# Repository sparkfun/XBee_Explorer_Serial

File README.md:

SparkFun XBee Explorer Serial
==============================

[*SparkFun XBee Explorer Serial (WRL-13225)*](https://www.sparkfun.com/products/9111)

This is a RS232 to serial base unit for the XBee line. 
It works with all XBee units, including Series 1, Series 2.5, standard and Pro versions.

Repository Contents
-------------------

* **/Hardware** - All Eagle design files (.brd, .sch, .STL)
* **/Production** - Production panel files (.brd)

Documentation
--------------
* **[Hookup Guide](https://learn.sparkfun.com/tutorials/exploring-xbees-and-xctu)** - Basic hookup guide for the XBee Serial Explorer.
* **[SparkFun Fritzing repo](https://github.com/sparkfun/Fritzing_Parts)** - Fritzing diagrams for SparkFun products.
* **[SparkFun 3D Model repo](https://github.com/sparkfun/3D_Models)** - 3D models of SparkFun products. 

Product Versions
----------------
* [WRL-13225](https://www.sparkfun.com/products/13225)- Version 1.4. Currently for sale. 
* [RWRL-09111](https://www.sparkfun.com/products/retired/9111)- Version 1.2. Retired. 

GitHub Version History
---------------
* [v1.4](https://github.com/sparkfun/XBee_Explorer_Serial/tree/v1.4) - Version 1.4. Current files. 
* [v1.3](https://github.com/sparkfun/XBee_Explorer_Serial/tree/v1.3) - Version 1.3. Retired.  
* [v1.2](https://github.com/sparkfun/XBee_Explorer_Serial/tree/v1.2) - Version 1.2. Retired. 

License Information
-------------------

This product is _**open source**_! 

Please review the LICENSE.md file for license information. 

If you have any questions or concerns on licensing, please contact techsupport@sparkfun.com.

Distributed as-is; no warranty is given.

- Your friends at SparkFun.

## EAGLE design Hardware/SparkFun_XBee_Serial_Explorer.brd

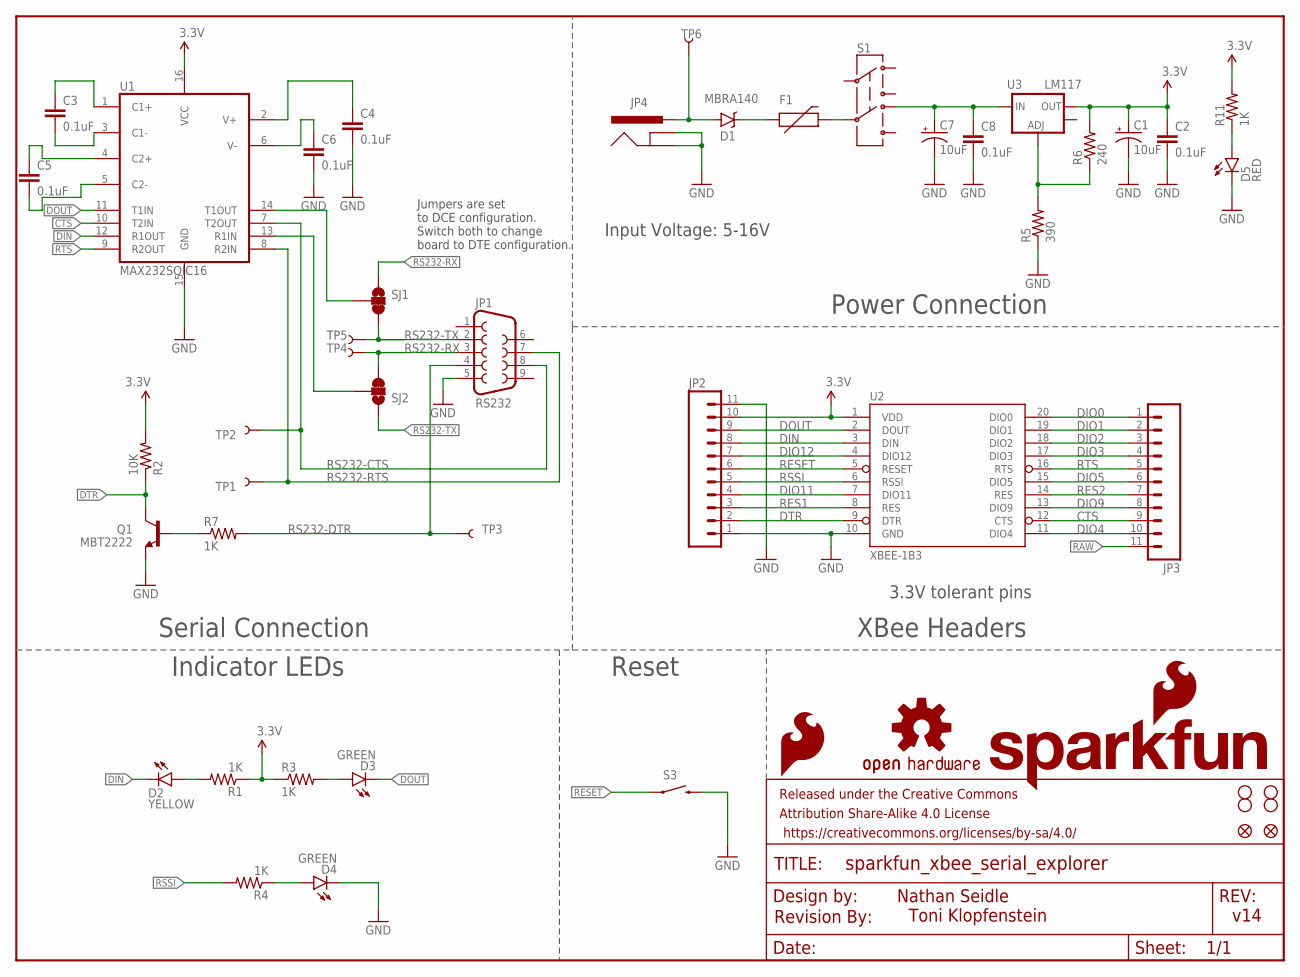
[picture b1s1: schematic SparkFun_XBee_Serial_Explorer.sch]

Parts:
C1, C7: 10uF; EIA3216
C2, C3, C4, C5, C6, C8: 0.1uF; 0603-CAP
D1: MBRA140; SMA-DIODE
D2: YELLOW; LED-1206
D3, D4: GREEN; LED-1206
D5: RED; LED-1206
F1: PTCTHERMISTOR1206; PTC-1206
FRAME1: FRAME-LETTER; CREATIVE_COMMONS
JP1: RS232; DB9
JP2, JP3: M11PTH; 1X11
JP4: POWER_JACKPTH_LOCK; POWER_JACK_PTH_LOCK
LOGO1: OSHW-LOGOL; OSHW-LOGO-L
LOGO2: SFE_LOGO_NAME_FLAME.2_INCH; SFE_LOGO_NAME_FLAME_.2
LOGO3: SFE_LOGO_FLAME.1_INCH; SFE_LOGO_FLAME_.1
Q1: MBT2222; SOT23-3
R1, R3, R4, R7, R11: 1K; 0603-RES
R2: 10K; 0603-RES
R5: 390; 0603-RES
R6: 240; 0603-RES
S1: AYZ0202
S3: TAC_SWITCHSMD; TACTILE-SWITCH-SMD
SJ1, SJ2: JUMPER-PAD-3-2OF3_NC_BY_TRACE_SMALL; PAD-JUMPER-3-2OF3_NC_BY_TRACE_YES_SILK_FULL_BOX
TP1, TP2, TP3, TP4, TP5, TP6: TEST-POINTTP_15TH_THRU; TP_15TH
U1: MAX232SOIC16; SO016
U2: XBEE-1B3; XBEE-SMD
U3: LM117; SOT223
U$1: REVISION
U$5, U$9, U$10, U$11: STAND-OFF
U$7, U$16: FIDUCIAL1X2; FIDUCIAL-1X2

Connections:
3.3V: C1.A (+), C2.1, JP2.10, R1.1, R2.2, R3.1, R6.2, R11.2, U1.16 (VCC), U2.1 (VDD), U3.2 (OUT)
CTS: JP3.9, U1.10 (T2IN), U2.12 (CTS)
DIN: D2.C, JP2.8, U1.12 (R1OUT), U2.3 (DIN)
DIO0: JP3.1, U2.20 (DIO0)
DIO1: JP3.2, U2.19 (DIO1)
DIO2: JP3.3, U2.18 (DIO2)
DIO3: JP3.4, U2.17 (DIO3)
DIO4: JP3.10, U2.11 (DIO4)
DIO5: JP3.6, U2.15 (DIO5)
DIO9: JP3.8, U2.13 (DIO9)
DIO11: JP2.4, U2.7 (DIO11)
DIO12: JP2.7, U2.4 (DIO12)
DOUT: D3.C, JP2.9, U1.11 (T1IN), U2.2 (DOUT)
DTR: JP2.2, Q1.3 (C), R2.1, U2.9 (DTR)
GND: C1.C (-), C2.2, C4.2, C6.2, C7.C (-), C8.2, D4.C, D5.C, JP1.5, JP2.1, JP2.11, JP4.GND, JP4.GNDBREAK, Q1.2 (E), R5.1, S3.3 (2), S3.4 (2), U1.15 (GND), U2.10 (GND)
unnamed: D2.A, R1.2
unnamed: D4.A, R4.1
unnamed: C3.1, U1.1 (C1+)
unnamed: D3.A, R3.2
unnamed: C3.2, U1.3 (C1-)
unnamed: C5.1, U1.4 (C2+)
unnamed: C5.2, U1.5 (C2-)
unnamed: C6.1, U1.6 (V-)
unnamed: C4.1, U1.2 (V+)
unnamed: R5.2, R6.1, U3.1 (ADJ)
unnamed: F1.2, S1.5
unnamed: Q1.1 (B), R7.1
unnamed: SJ2.2, U1.13 (R1IN)
unnamed: SJ1.2, U1.14 (T1OUT)
unnamed: D1.A, JP4.PWR, TP6.P$1
unnamed: D1.C, F1.1
unnamed: D5.A, R11.1
RAW: C7.A (+), C8.1, JP3.11, S1.6 (4), U3.3 (IN)
RES1: JP2.3, U2.8 (RES)
RES2: JP3.7, U2.14 (RES)
RESET: JP2.6, S3.1, S3.2 (1), U2.5 (RESET)
RS232-CTS: JP1.8, TP2.P$1, U1.7 (T2OUT)
RS232-DTR: JP1.4, R7.2, TP3.P$1
RS232-RTS: JP1.7, TP1.P$1, U1.8 (R2IN)
RS232-RX: JP1.3, SJ1.1, SJ2.3, TP4.P$1
RS232-TX: JP1.2, SJ1.3, SJ2.1, TP5.P$1
RSSI: JP2.5, R4.2, U2.6 (RSSI)
RTS: JP3.5, U1.9 (R2OUT), U2.16 (RTS)

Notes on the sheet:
v14
Nathan Seidle
Toni Klopfenstein
Jumpers are set to DCE configuration. Switch both to change board to DTE configuration.
Input Voltage: 5-16V
3.3V tolerant pins
Serial Connection
Power Connection
XBee Headers
Reset
Indicator LEDs

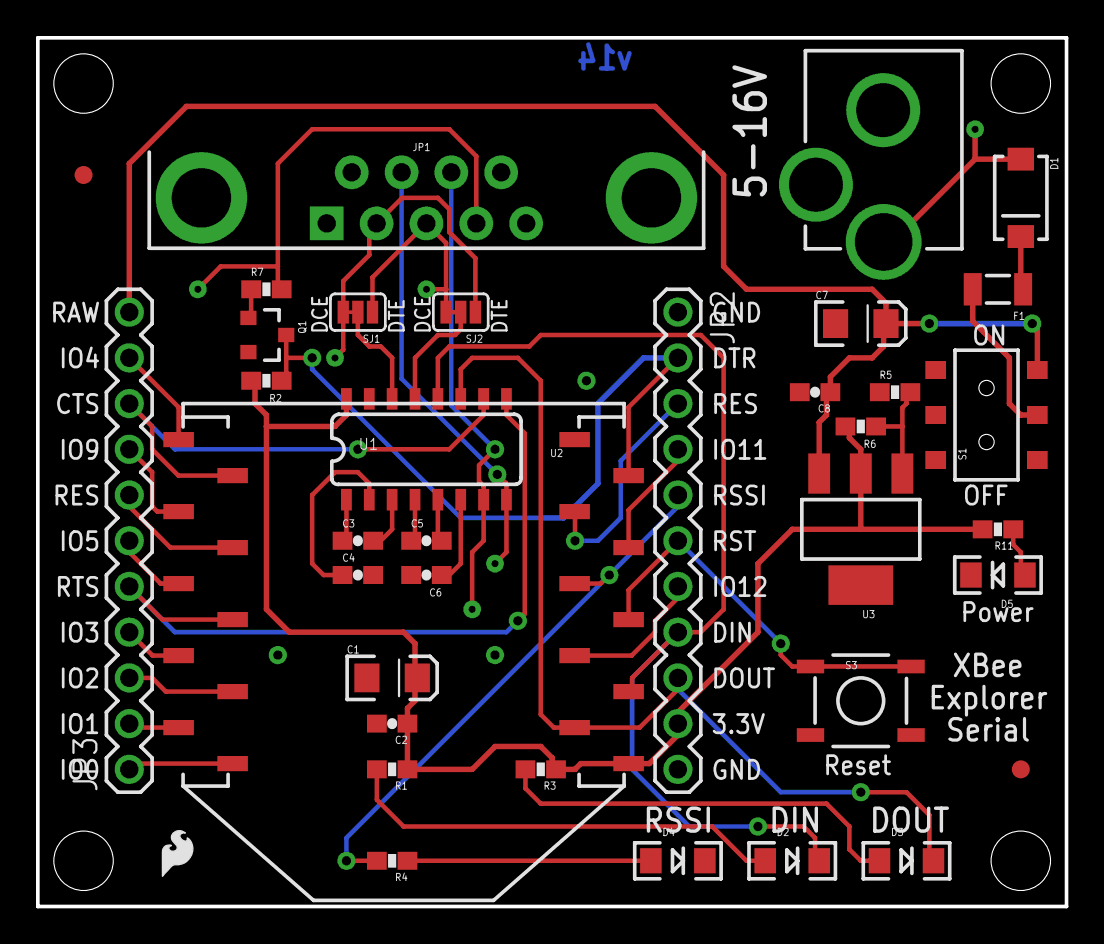
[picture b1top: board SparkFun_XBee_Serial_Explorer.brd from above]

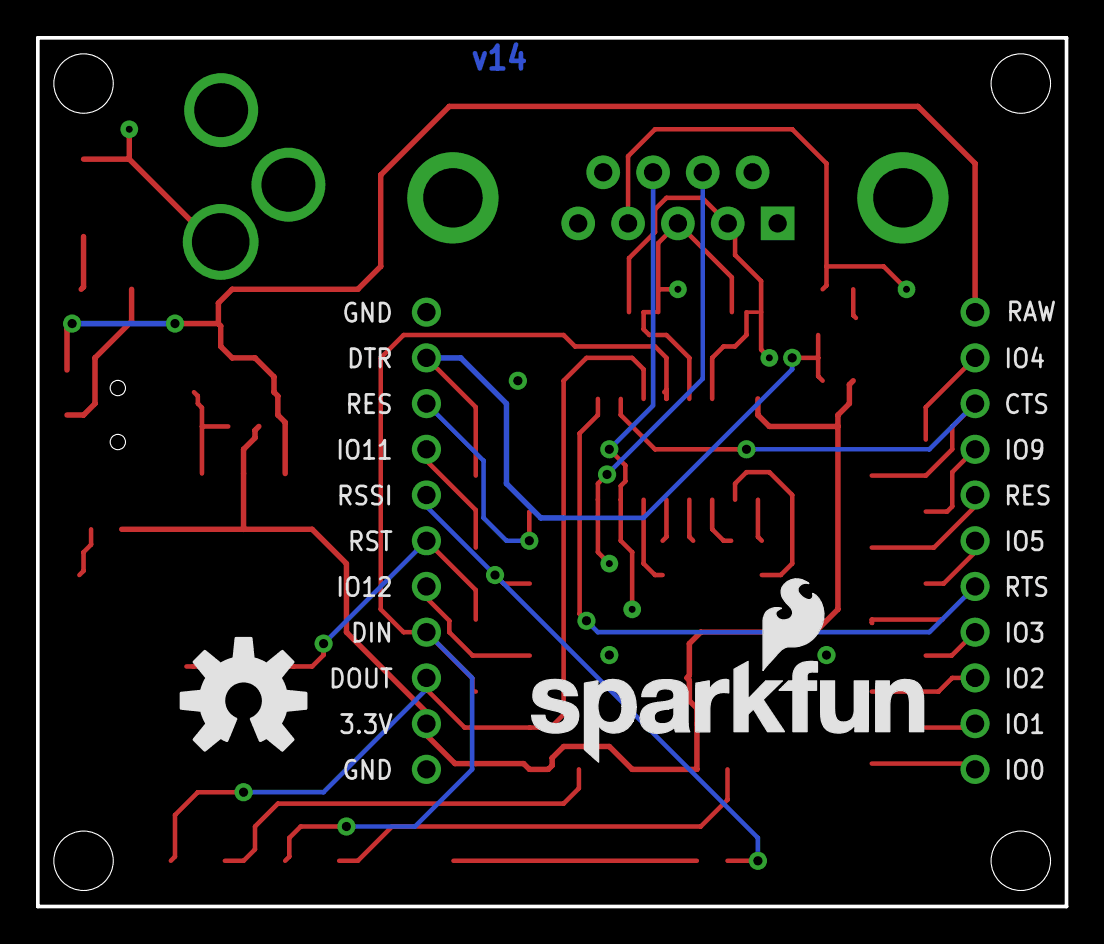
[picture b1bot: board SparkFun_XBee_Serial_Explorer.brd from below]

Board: 2 copper layers, 57.1 x 48.3 mm, 51 parts (2 on the bottom side), 43 nets.

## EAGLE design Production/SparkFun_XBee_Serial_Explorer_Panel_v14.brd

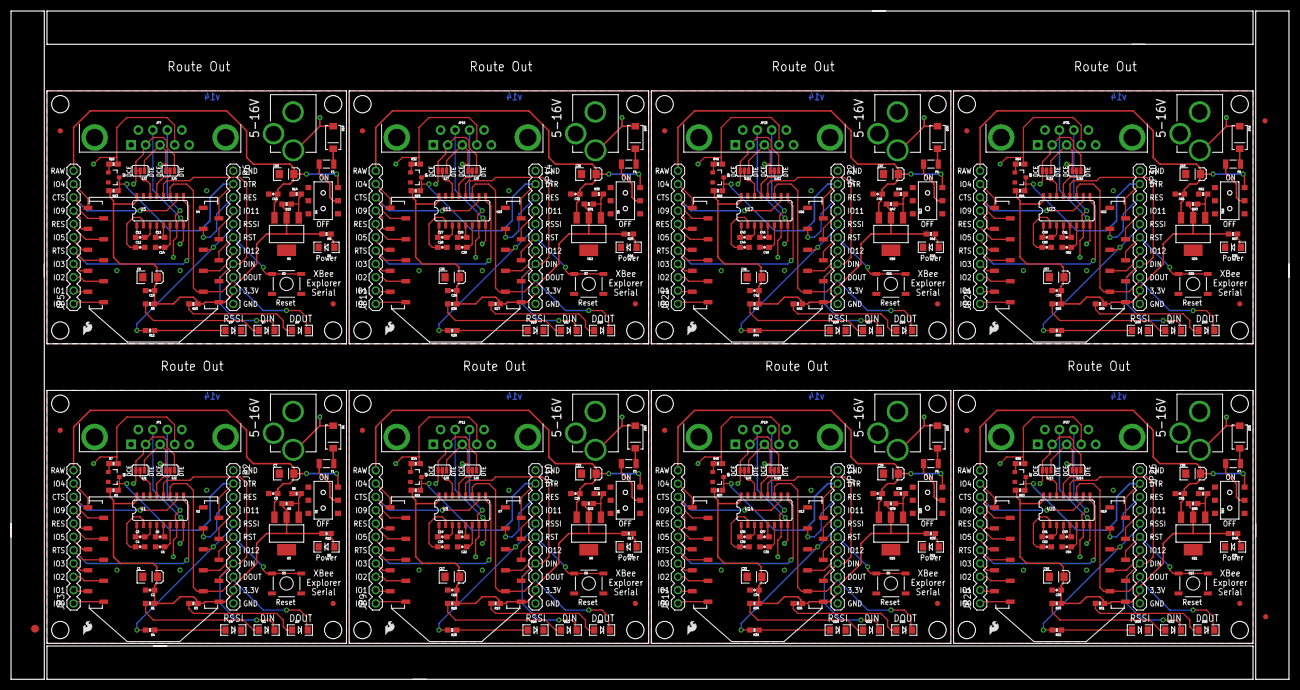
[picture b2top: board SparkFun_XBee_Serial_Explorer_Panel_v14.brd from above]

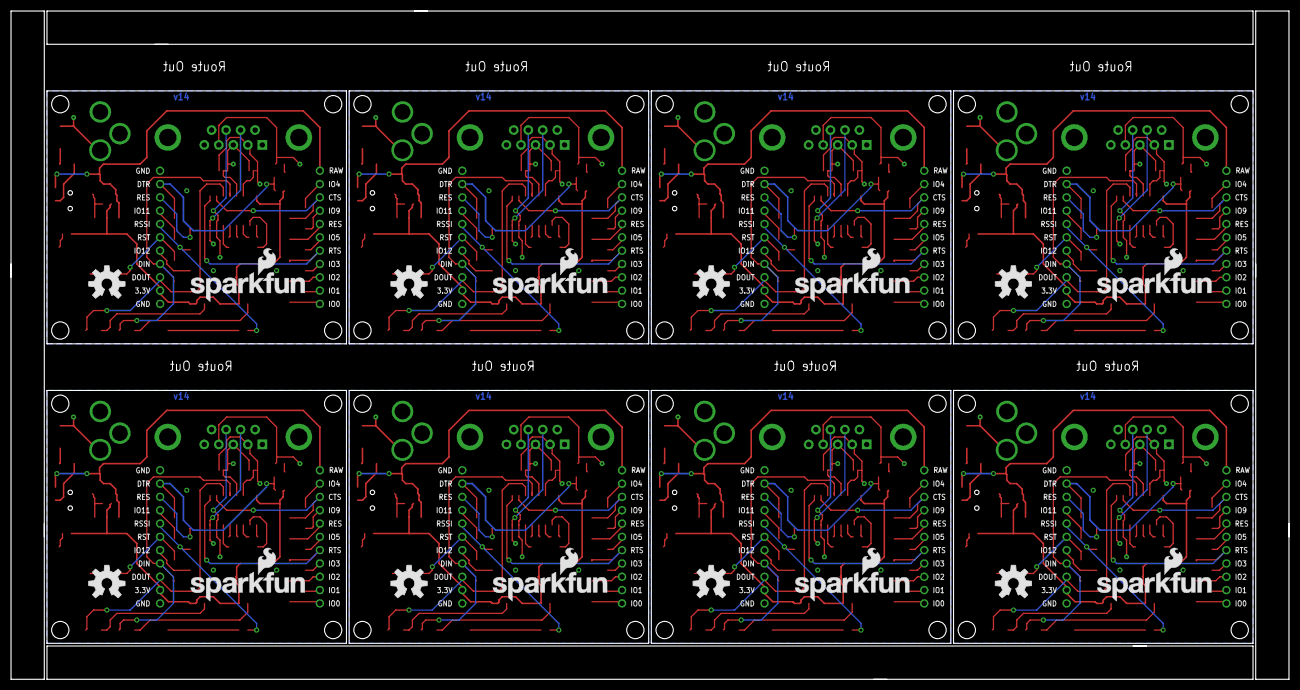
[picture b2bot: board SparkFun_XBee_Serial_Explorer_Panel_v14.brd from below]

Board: 2 copper layers, 243.8 x 127.5 mm, 395 parts (16 on the bottom side), 344 nets.

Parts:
C1, C7, C9, C15, C17, C23, C25, C31, C33, C39, C41, C47, C49, C55, C57, C63: 10uF; EIA3216
C2, C3, C4, C5, C6, C8, C10, C11, C12, C13, C14, C16, C18, C19, C20, C21, C22, C24, C26, C27, C28, C29, C30, C32, C34, C35, C36, C37, C38, C40, C42, C43, C44, C45, C46, C48, C50, C51, C52, C53, C54, C56, C58, C59, C60, C61, C62, C64: 0.1uF; 0603-CAP
D1, D10, D15, D20, D25, D30, D35, D40: MBRA140; SMA-DIODE
D2, D7, D12, D17, D22, D27, D32, D37: YELLOW; LED-1206
D3, D4, D8, D9, D13, D14, D18, D19, D23, D24, D28, D29, D33, D34, D38, D39: GREEN; LED-1206
D5, D6, D11, D16, D21, D26, D31, D36: RED; LED-1206
E$1: FIDUCIAL-1.5X3
E$5, E$6: FIDUCIAL-1X2
F1, F2, F3, F4, F5, F6, F7, F8: PTCTHERMISTOR1206; PTC-1206
JP1, JP7, JP11, JP15, JP19, JP23, JP27, JP31: RS232; DB9
JP2, JP3, JP5, JP6, JP9, JP10, JP13, JP14, JP17, JP18, JP21, JP22, JP25, JP26, JP29, JP30: 1X11
JP4, JP8, JP12, JP16, JP20, JP24, JP28, JP32: POWER_JACKPTH_LOCK; POWER_JACK_PTH_LOCK
LOGO1, LOGO4, LOGO7, LOGO10, LOGO13, LOGO16, LOGO19, LOGO22: OSHW-LOGOL; OSHW-LOGO-L
LOGO2, LOGO5, LOGO8, LOGO11, LOGO14, LOGO17, LOGO20, LOGO23: SFE_LOGO_NAME_FLAME.2_INCH; SFE_LOGO_NAME_FLAME_.2
LOGO3, LOGO6, LOGO9, LOGO12, LOGO15, LOGO18, LOGO21, LOGO24: SFE_LOGO_FLAME.1_INCH; SFE_LOGO_FLAME_.1
Q1, Q2, Q3, Q4, Q5, Q6, Q7, Q8: MBT2222; SOT23-3
R1, R3, R4, R7, R8, R9, R10, R11, R12, R16, R17, R18, R19, R20, R24, R25, R26, R27, R28, R32, R33, R34, R35, R36, R40, R41, R42, R43, R44, R48, R49, R50, R51, R52, R56, R57, R58, R59, R60, R64: 1K; 0603-RES
R2, R13, R21, R29, R37, R45, R53, R61: 10K; 0603-RES
R5, R14, R22, R30, R38, R46, R54, R62: 390; 0603-RES
R6, R15, R23, R31, R39, R47, R55, R63: 240; 0603-RES
S1, S4, S6, S8, S10, S12, S14, S16: AYZ0202
S2, S3, S5, S7, S9, S11, S13, S15: TAC_SWITCHSMD; TACTILE-SWITCH-SMD
SJ1, SJ2, SJ3, SJ4, SJ5, SJ6, SJ7, SJ8, SJ9, SJ10, SJ11, SJ12, SJ13, SJ14, SJ15, SJ16: JUMPER-PAD-3-2OF3_NC_BY_TRACE_SMALL; PAD-JUMPER-3-2OF3_NC_BY_TRACE_YES_SILK_FULL_BOX
TP1, TP2, TP3, TP4, TP5, TP6, TP7, TP8, TP9, TP10, TP11, TP12, TP13, TP14, TP15, TP16, TP17, TP18, TP19, TP20, TP21, TP22, TP23, TP24, TP25, TP26, TP27, TP28, TP29, TP30, TP31, TP32, TP33, TP34, TP35, TP36, TP37, TP38, TP39, TP40, TP41, TP42, TP43, TP44, TP45, TP46, TP47, TP48: TEST-POINTTP_15TH_THRU; TP_15TH
U1, U5, U8, U11, U14, U17, U20, U23: MAX232SOIC16; SO016
U2, U4, U7, U10, U13, U16, U19, U22: XBEE-1B3; XBEE-SMD
U3, U6, U9, U12, U15, U18, U21, U24: LM117; SOT223
U$1, U$2, U$7, U$12, U$13, U$16, U$19, U$20, U$25, U$26, U$31, U$32, U$37, U$38, U$43, U$44: FIDUCIAL1X2; FIDUCIAL-1X2
U$3, U$4, U$5, U$6, U$8, U$9, U$10, U$11, U$14, U$15, U$17, U$18, U$21, U$22, U$23, U$24, U$27, U$28, U$29, U$30, U$33, U$34, U$35, U$36, U$39, U$40, U$41, U$42, U$45, U$46, U$47, U$48: STAND-OFF

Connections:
3.3V: C1.A, C2.1, JP2.10, R1.1, R2.2, R3.1, R6.2, R11.2, U1.16, U2.1, U3.2
3.3V1: C9.A, C10.1, JP6.10, R8.2, R9.1, R10.1, R13.2, R15.2, U4.1, U5.16, U6.2
3.3V2: C17.A, C18.1, JP10.10, R17.2, R18.1, R19.1, R21.2, R23.2, U7.1, U8.16, U9.2
3.3V3: C25.A, C26.1, JP14.10, R25.2, R26.1, R27.1, R29.2, R31.2, U10.1, U11.16, U12.2
3.3V4: C33.A, C34.1, JP18.10, R33.2, R34.1, R35.1, R37.2, R39.2, U13.1, U14.16, U15.2
3.3V5: C41.A, C42.1, JP22.10, R41.2, R42.1, R43.1, R45.2, R47.2, U16.1, U17.16, U18.2
3.3V6: C49.A, C50.1, JP26.10, R49.2, R50.1, R51.1, R53.2, R55.2, U19.1, U20.16, U21.2
3.3V7: C57.A, C58.1, JP30.10, R57.2, R58.1, R59.1, R61.2, R63.2, U22.1, U23.16, U24.2
CTS: JP3.9, U1.10, U2.12
CTS1: JP5.9, U4.12, U5.10
CTS2: JP9.9, U7.12, U8.10
CTS3: JP13.9, U10.12, U11.10
CTS4: JP17.9, U13.12, U14.10
CTS5: JP21.9, U16.12, U17.10
CTS6: JP25.9, U19.12, U20.10
CTS7: JP29.9, U22.12, U23.10
DIN: D2.C, JP2.8, U1.12, U2.3
DIN1: D7.C, JP6.8, U4.3, U5.12
DIN2: D12.C, JP10.8, U7.3, U8.12
DIN3: D17.C, JP14.8, U10.3, U11.12
DIN4: D22.C, JP18.8, U13.3, U14.12
DIN5: D27.C, JP22.8, U16.3, U17.12
DIN6: D32.C, JP26.8, U19.3, U20.12
DIN7: D37.C, JP30.8, U22.3, U23.12
DIO0: JP3.1, U2.20
DIO1: JP3.2, U2.19
DIO2: JP3.3, U2.18
DIO3: JP3.4, U2.17
DIO4: JP3.10, U2.11
DIO5: JP3.6, U2.15
DIO6: JP5.10, U4.11
DIO7: JP5.8, U4.13
DIO8: JP5.6, U4.15
DIO9: JP3.8, U2.13
DIO10: JP5.4, U4.17
DIO11: JP2.4, U2.7
DIO12: JP2.7, U2.4
DIO13: JP5.3, U4.18
DIO14: JP5.2, U4.19
DIO15: JP5.1, U4.20
DIO16: JP6.4, U4.7
DIO17: JP6.7, U4.4
DIO18: JP9.10, U7.11
DIO19: JP9.8, U7.13
DIO20: JP9.6, U7.15
DIO21: JP9.4, U7.17
DIO22: JP9.3, U7.18
DIO23: JP9.2, U7.19
DIO24: JP9.1, U7.20
DIO25: JP10.4, U7.7
DIO26: JP10.7, U7.4
DIO27: JP13.10, U10.11
DIO28: JP13.8, U10.13
DIO29: JP13.6, U10.15
DIO30: JP13.4, U10.17
DIO31: JP13.3, U10.18
DIO32: JP13.2, U10.19
DIO33: JP13.1, U10.20
DIO34: JP14.4, U10.7
DIO35: JP14.7, U10.4
DIO36: JP17.10, U13.11
DIO37: JP17.8, U13.13
DIO38: JP17.6, U13.15
DIO39: JP17.4, U13.17
DIO40: JP17.3, U13.18
DIO41: JP17.2, U13.19
DIO42: JP17.1, U13.20
DIO43: JP18.4, U13.7
DIO44: JP18.7, U13.4
DIO45: JP21.10, U16.11
DIO46: JP21.8, U16.13
DIO47: JP21.6, U16.15
DIO48: JP21.4, U16.17
DIO49: JP21.3, U16.18
DIO50: JP21.2, U16.19
DIO51: JP21.1, U16.20
DIO52: JP22.4, U16.7
DIO53: JP22.7, U16.4
DIO54: JP25.10, U19.11
DIO55: JP25.8, U19.13
DIO56: JP25.6, U19.15
DIO57: JP25.4, U19.17
DIO58: JP25.3, U19.18
DIO59: JP25.2, U19.19
DIO60: JP25.1, U19.20
DIO61: JP26.4, U19.7
DIO62: JP26.7, U19.4
DIO63: JP29.10, U22.11
DIO64: JP29.8, U22.13
DIO65: JP29.6, U22.15
DIO66: JP29.4, U22.17
DIO67: JP29.3, U22.18
DIO68: JP29.2, U22.19
DIO69: JP29.1, U22.20
DIO70: JP30.4, U22.7
DIO71: JP30.7, U22.4
DOUT: D3.C, JP2.9, U1.11, U2.2
DOUT1: D8.C, JP6.9, U4.2, U5.11
DOUT2: D13.C, JP10.9, U7.2, U8.11
DOUT3: D18.C, JP14.9, U10.2, U11.11
DOUT4: D23.C, JP18.9, U13.2, U14.11
DOUT5: D28.C, JP22.9, U16.2, U17.11
DOUT6: D33.C, JP26.9, U19.2, U20.11
DOUT7: D38.C, JP30.9, U22.2, U23.11
DTR: JP2.2, Q1.3, R2.1, U2.9
DTR1: JP6.2, Q2.3, R13.1, U4.9
DTR2: JP10.2, Q3.3, R21.1, U7.9
DTR3: JP14.2, Q4.3, R29.1, U10.9
DTR4: JP18.2, Q5.3, R37.1, U13.9
DTR5: JP22.2, Q6.3, R45.1, U16.9
DTR6: JP26.2, Q7.3, R53.1, U19.9
DTR7: JP30.2, Q8.3, R61.1, U22.9
GND: C1.C, C2.2, C4.2, C6.2, C7.C, C8.2, D4.C, D5.C, JP1.5, JP2.1, JP2.11, JP4.GND, JP4.GNDBREAK, Q1.2, R5.1, S3.3, S3.4, U1.15, U2.10
GND1: C9.C, C10.2, C12.2, C14.2, C15.C, C16.2, D6.C, D9.C, JP6.1, JP6.11, JP7.5, JP8.GND, JP8.GNDBREAK, Q2.2, R14.1, S2.3, S2.4, U4.10, U5.15
GND2: C17.C, C18.2, C20.2, C22.2, C23.C, C24.2, D11.C, D14.C, JP10.1, JP10.11, JP11.5, JP12.GND, JP12.GNDBREAK, Q3.2, R22.1, S5.3, S5.4, U7.10, U8.15
GND3: C25.C, C26.2, C28.2, C30.2, C31.C, C32.2, D16.C, D19.C, JP14.1, JP14.11, JP15.5, JP16.GND, JP16.GNDBREAK, Q4.2, R30.1, S7.3, S7.4, U10.10, U11.15
GND4: C33.C, C34.2, C36.2, C38.2, C39.C, C40.2, D21.C, D24.C, JP18.1, JP18.11, JP19.5, JP20.GND, JP20.GNDBREAK, Q5.2, R38.1, S9.3, S9.4, U13.10, U14.15
GND5: C41.C, C42.2, C44.2, C46.2, C47.C, C48.2, D26.C, D29.C, JP22.1, JP22.11, JP23.5, JP24.GND, JP24.GNDBREAK, Q6.2, R46.1, S11.3, S11.4, U16.10, U17.15
GND6: C49.C, C50.2, C52.2, C54.2, C55.C, C56.2, D31.C, D34.C, JP26.1, JP26.11, JP27.5, JP28.GND, JP28.GNDBREAK, Q7.2, R54.1, S13.3, S13.4, U19.10, U20.15
GND7: C57.C, C58.2, C60.2, C62.2, C63.C, C64.2, D36.C, D39.C, JP30.1, JP30.11, JP31.5, JP32.GND, JP32.GNDBREAK, Q8.2, R62.1, S15.3, S15.4, U22.10, U23.15
unnamed: D2.A, R1.2
unnamed: D4.A, R4.1
unnamed: C3.1, U1.1
unnamed: D3.A, R3.2
unnamed: C3.2, U1.3
unnamed: C5.1, U1.4
unnamed: C5.2, U1.5
unnamed: C6.1, U1.6
unnamed: C4.1, U1.2
unnamed: R5.2, R6.1, U3.1
unnamed: F1.2, S1.5
unnamed: Q1.1, R7.1
unnamed: SJ2.2, U1.13
unnamed: SJ1.2, U1.14
unnamed: D1.A, JP4.PWR, TP6.P$1
unnamed: D1.C, F1.1
unnamed: D6.A, R8.1
unnamed: D7.A, R9.2
unnamed: D8.A, R10.2
unnamed: D9.A, R12.1
unnamed: C11.2, U5.3
unnamed: C13.1, U5.4
unnamed: C13.2, U5.5
unnamed: C14.1, U5.6
unnamed: C12.1, U5.2
unnamed: C11.1, U5.1
unnamed: D10.A, JP8.PWR, TP12.P$1
unnamed: D10.C, F2.1
unnamed: R14.2, R15.1, U6.1
unnamed: F2.2, S4.5
unnamed: Q2.1, R16.1
unnamed: SJ4.2, U5.13
unnamed: SJ3.2, U5.14
unnamed: D11.A, R17.1
unnamed: D12.A, R18.2
unnamed: D13.A, R19.2
unnamed: D14.A, R20.1
unnamed: D5.A, R11.1
unnamed: C19.2, U8.3
unnamed: C21.1, U8.4
unnamed: C21.2, U8.5
unnamed: C22.1, U8.6
unnamed: C20.1, U8.2
unnamed: C19.1, U8.1
unnamed: D15.A, JP12.PWR, TP18.P$1
unnamed: D15.C, F3.1
unnamed: R22.2, R23.1, U9.1
unnamed: F3.2, S6.5
unnamed: Q3.1, R24.1
unnamed: SJ6.2, U8.13
unnamed: SJ5.2, U8.14
unnamed: D16.A, R25.1
unnamed: D17.A, R26.2
unnamed: D18.A, R27.2
unnamed: D19.A, R28.1
unnamed: C27.2, U11.3
unnamed: C29.1, U11.4
unnamed: C29.2, U11.5
unnamed: C30.1, U11.6
unnamed: C28.1, U11.2
unnamed: C27.1, U11.1
unnamed: D20.A, JP16.PWR, TP24.P$1
unnamed: D20.C, F4.1
unnamed: R30.2, R31.1, U12.1
unnamed: F4.2, S8.5
unnamed: Q4.1, R32.1
unnamed: SJ8.2, U11.13
unnamed: SJ7.2, U11.14
unnamed: D21.A, R33.1
unnamed: D22.A, R34.2
unnamed: D23.A, R35.2
unnamed: D24.A, R36.1
unnamed: C35.2, U14.3
unnamed: C37.1, U14.4
unnamed: C37.2, U14.5
unnamed: C38.1, U14.6
unnamed: C36.1, U14.2
unnamed: C35.1, U14.1
unnamed: D25.A, JP20.PWR, TP30.P$1
unnamed: D25.C, F5.1
unnamed: R38.2, R39.1, U15.1
unnamed: F5.2, S10.5
unnamed: Q5.1, R40.1
unnamed: SJ10.2, U14.13
unnamed: SJ9.2, U14.14
unnamed: D26.A, R41.1
unnamed: D27.A, R42.2
unnamed: D28.A, R43.2
unnamed: D29.A, R44.1
unnamed: C43.2, U17.3
unnamed: C45.1, U17.4
unnamed: C45.2, U17.5
unnamed: C46.1, U17.6
unnamed: C44.1, U17.2
unnamed: C43.1, U17.1
unnamed: D30.A, JP24.PWR, TP36.P$1
unnamed: D30.C, F6.1
unnamed: R46.2, R47.1, U18.1
unnamed: F6.2, S12.5
unnamed: Q6.1, R48.1
unnamed: SJ12.2, U17.13
unnamed: SJ11.2, U17.14
unnamed: D31.A, R49.1
unnamed: D32.A, R50.2
unnamed: D33.A, R51.2
unnamed: D34.A, R52.1
unnamed: C51.2, U20.3
unnamed: C53.1, U20.4
unnamed: C53.2, U20.5
unnamed: C54.1, U20.6
unnamed: C52.1, U20.2
unnamed: C51.1, U20.1
unnamed: D35.A, JP28.PWR, TP42.P$1
unnamed: D35.C, F7.1
unnamed: R54.2, R55.1, U21.1
unnamed: F7.2, S14.5
unnamed: Q7.1, R56.1
unnamed: SJ14.2, U20.13
unnamed: SJ13.2, U20.14
unnamed: D36.A, R57.1
unnamed: D37.A, R58.2
unnamed: D38.A, R59.2
unnamed: D39.A, R60.1
unnamed: C59.2, U23.3
unnamed: C61.1, U23.4
unnamed: C61.2, U23.5
unnamed: C62.1, U23.6
unnamed: C60.1, U23.2
unnamed: C59.1, U23.1
unnamed: D40.A, JP32.PWR, TP48.P$1
unnamed: D40.C, F8.1
unnamed: R62.2, R63.1, U24.1
unnamed: F8.2, S16.5
unnamed: Q8.1, R64.1
unnamed: SJ16.2, U23.13
unnamed: SJ15.2, U23.14
RAW: C7.A, C8.1, JP3.11, S1.6, U3.3
RAW1: C15.A, C16.1, JP5.11, S4.6, U6.3
RAW2: C23.A, C24.1, JP9.11, S6.6, U9.3
RAW3: C31.A, C32.1, JP13.11, S8.6, U12.3
RAW4: C39.A, C40.1, JP17.11, S10.6, U15.3
RAW5: C47.A, C48.1, JP21.11, S12.6, U18.3
RAW6: C55.A, C56.1, JP25.11, S14.6, U21.3
RAW7: C63.A, C64.1, JP29.11, S16.6, U24.3
RES1: JP2.3, U2.8
RES2: JP3.7, U2.14
RES3: JP6.3, U4.8
RES4: JP5.7, U4.14
RES5: JP10.3, U7.8
RES6: JP9.7, U7.14
RES7: JP14.3, U10.8
RES8: JP13.7, U10.14
RES9: JP18.3, U13.8
RES10: JP17.7, U13.14
RES11: JP22.3, U16.8
RES12: JP21.7, U16.14
RES13: JP26.3, U19.8
RES14: JP25.7, U19.14
RES15: JP30.3, U22.8
RES16: JP29.7, U22.14
RESET: JP2.6, S3.1, S3.2, U2.5
RESET1: JP6.6, S2.1, S2.2, U4.5
RESET2: JP10.6, S5.1, S5.2, U7.5
RESET3: JP14.6, S7.1, S7.2, U10.5
RESET4: JP18.6, S9.1, S9.2, U13.5
RESET5: JP22.6, S11.1, S11.2, U16.5
RESET6: JP26.6, S13.1, S13.2, U19.5
RESET7: JP30.6, S15.1, S15.2, U22.5
RS232-CTS: JP1.8, TP2.P$1, U1.7
RS232-CTS1: JP7.8, TP8.P$1, U5.7
RS232-CTS2: JP11.8, TP14.P$1, U8.7
RS232-CTS3: JP15.8, TP20.P$1, U11.7
RS232-CTS4: JP19.8, TP26.P$1, U14.7
RS232-CTS5: JP23.8, TP32.P$1, U17.7
RS232-CTS6: JP27.8, TP38.P$1, U20.7
RS232-CTS7: JP31.8, TP44.P$1, U23.7
RS232-DTR: JP1.4, R7.2, TP3.P$1
RS232-DTR1: JP7.4, R16.2, TP9.P$1
RS232-DTR2: JP11.4, R24.2, TP15.P$1
RS232-DTR3: JP15.4, R32.2, TP21.P$1
RS232-DTR4: JP19.4, R40.2, TP27.P$1
RS232-DTR5: JP23.4, R48.2, TP33.P$1
RS232-DTR6: JP27.4, R56.2, TP39.P$1
RS232-DTR7: JP31.4, R64.2, TP45.P$1
RS232-RTS: JP1.7, TP1.P$1, U1.8
RS232-RTS1: JP7.7, TP7.P$1, U5.8
RS232-RTS2: JP11.7, TP13.P$1, U8.8
RS232-RTS3: JP15.7, TP19.P$1, U11.8
RS232-RTS4: JP19.7, TP25.P$1, U14.8
RS232-RTS5: JP23.7, TP31.P$1, U17.8
RS232-RTS6: JP27.7, TP37.P$1, U20.8
RS232-RTS7: JP31.7, TP43.P$1, U23.8
RS232-RX: JP1.3, SJ1.1, SJ2.3, TP4.P$1
RS232-RX1: JP7.3, SJ3.1, SJ4.3, TP10.P$1
RS232-RX2: JP11.3, SJ5.1, SJ6.3, TP16.P$1
RS232-RX3: JP15.3, SJ7.1, SJ8.3, TP22.P$1
RS232-RX4: JP19.3, SJ9.1, SJ10.3, TP28.P$1
RS232-RX5: JP23.3, SJ11.1, SJ12.3, TP34.P$1
RS232-RX6: JP27.3, SJ13.1, SJ14.3, TP40.P$1
RS232-RX7: JP31.3, SJ15.1, SJ16.3, TP46.P$1
RS232-TX: JP1.2, SJ1.3, SJ2.1, TP5.P$1
RS232-TX1: JP7.2, SJ3.3, SJ4.1, TP11.P$1
RS232-TX2: JP11.2, SJ5.3, SJ6.1, TP17.P$1
RS232-TX3: JP15.2, SJ7.3, SJ8.1, TP23.P$1
RS232-TX4: JP19.2, SJ9.3, SJ10.1, TP29.P$1
RS232-TX5: JP23.2, SJ11.3, SJ12.1, TP35.P$1
RS232-TX6: JP27.2, SJ13.3, SJ14.1, TP41.P$1
RS232-TX7: JP31.2, SJ15.3, SJ16.1, TP47.P$1
RSSI: JP2.5, R4.2, U2.6
RSSI1: JP6.5, R12.2, U4.6
RSSI2: JP10.5, R20.2, U7.6
RSSI3: JP14.5, R28.2, U10.6
RSSI4: JP18.5, R36.2, U13.6
RSSI5: JP22.5, R44.2, U16.6
RSSI6: JP26.5, R52.2, U19.6
RSSI7: JP30.5, R60.2, U22.6
RTS: JP3.5, U1.9, U2.16
RTS1: JP5.5, U4.16, U5.9
RTS2: JP9.5, U7.16, U8.9
RTS3: JP13.5, U10.16, U11.9
RTS4: JP17.5, U13.16, U14.9
RTS5: JP21.5, U16.16, U17.9
RTS6: JP25.5, U19.16, U20.9
RTS7: JP29.5, U22.16, U23.9

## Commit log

2014-11-07 Initial hardware files added and README updated.
2014-11-08 Initial schematic updates to new library parts
2014-11-11 Board rev in progress
2014-11-13 Rerouting, updating parts to PTH, add dimensions, etc.
2014-11-18 Updating board and schematic to address GitHub issues
2014-11-19 Fixes for QC checklist
2014-11-19 Moving barrel jack silk
2014-11-21 Adding in test points for QC
2014-11-21 Fixing PTC part number for proper BOM
2014-12-29 Moving test points away from selective solder points/moving board name
2014-12-30 Final QC checklist and changes for testbed
2015-01-07 moved fids slightly
2015-01-07 created v13 giant panel
2015-10-27 Update repo structure, readme with new product info, add license file
2015-10-27 Update README.md
    Fixing product image.
2015-10-27 Update README.md
    Fixing product sku.
2016-02-12 Fixing jumper trace, updating version number
2016-03-01 Fixing silk logos to prevent large plot data issues
2016-03-01 created panel v14
2016-04-25 Updating README and license file

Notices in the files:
parts and their libraries:
SparkFun-Aesthetics: Licensing: Creative Commons ShareAlike 4.0 International - https://creativecommons.org/licenses/by-sa/4.0
SparkFun-Aesthetics: Released under the Creative Commons Attribution Share-Alike 4.0 License
SparkFun-Aesthetics: https://creativecommons.org/licenses/by-sa/4.0
